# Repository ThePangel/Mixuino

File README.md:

<h1 align="center">Mixuino</h1>

<h3 align="center">An Arduino Mixer for windows built with Python</h3>

-----------

- Table of contents
	- Description
	- Built with
	- Usage
		- UI
		- Config file
	- Getting started
		- Software
			- Required libraries
			- Python
		- Hardware
			- Required hardware
			- Circuit diagram
	- Roadmap!
	- Contributing?
	- Contact
	- Acknowledgement/Credit

---------

Mixuino is a windows audio mixer build with on a Arduino nano and controlled by a python program. It uses 4 slide potentiometers feeding analog input into an Arduino nano that sends the values through serial to a python scripts that handles volume management in the windows machine. You can also add an optional push button to mute/un-mute the speakers. 

I also have made a PCB for ease of instalation + a 3D printable enclosure for the latter so you can build your own Mixer.

This is my first Arduino projects and first *"big"* program so please bear with me :)

-----
## Built with:

- 
- 
- 

---
## Usage 

### UI

Each checkbox corresponds to a running process and/or a process stored in the config file, ones stored (therefore selected) are checked, moving that slider will change the volume of selected processes (1<sup>st</sup> slider is for master volume)

Hide to systray hides the window, the window can be revealed again from the systray icon option  ``Show`` 

There is also a checkbox than when checked changes the ``hideDefault`` value if you want the window to be hidden at startup

The options available refreshes and changes (if new programs are opened or others closed) when the mouse hovers any of the scrollable frames

To close the application you can just close this window or close it with the ``Exit`` option in the systray icon

### Config file

To run the program you require [processes.yaml](processes.yaml) file with the structure : 
```yaml
hideDefault: false
slider1: []	
slider2: []
slider3: []

```
The values are the processes each slide changes and can be changed manually or through the UI

---
## Getting started

### Software

#### Required libraries:

##### Python
- Using pip

```python
comtypes==1.2.0 # To communicate with the ports

Pillow==10.1.0 # For opening the image for the systray icon

pycaw==20230407 # For audio handling

pyserial==3.5 # To read the serial data sent from the arduino

pystray==0.19.5 # To create and manage the systray icon

PyYAML==6.0.1 # To edit the Yaml config file

customtkinter==5.2.1 # To build the UI
```

```console
pip install comtypes

pip install Pillow

pip install pycaw

pip install pyserial

pip install pystray

pip install PyYAML

pip install customtkinter
```
##### Nothing needed for the Arduino

### Hardware 
#### Required hardware

- Arduino nano (you could use any Arduino tho)
- 4 (or more if you want to expand) slide potentiometers
- Optional push button for muting

##### Circuit diagram

---

## Roadmap!

- [x] Slider 3D Models for 3D printing! (7/7/2024)
- [x] GUI to select which slides control which process (30/12/2023)
- [x] Mixuino PCB (7/7/2024)

---
## Contributing?

- Feel free to open up any issues or ask for features in the issues tab!
- If you want to contribute directly make sure to fork the repo and submit a pull request for me to review.

---
## Contact

Feel free to contact me [@ThePangel_](https://twitter.com/thepangel_) on Twitter/X or DM me on discord @thepangel

----
## Acknowledgement/Credit

- Logo: Inés D'Olha

---

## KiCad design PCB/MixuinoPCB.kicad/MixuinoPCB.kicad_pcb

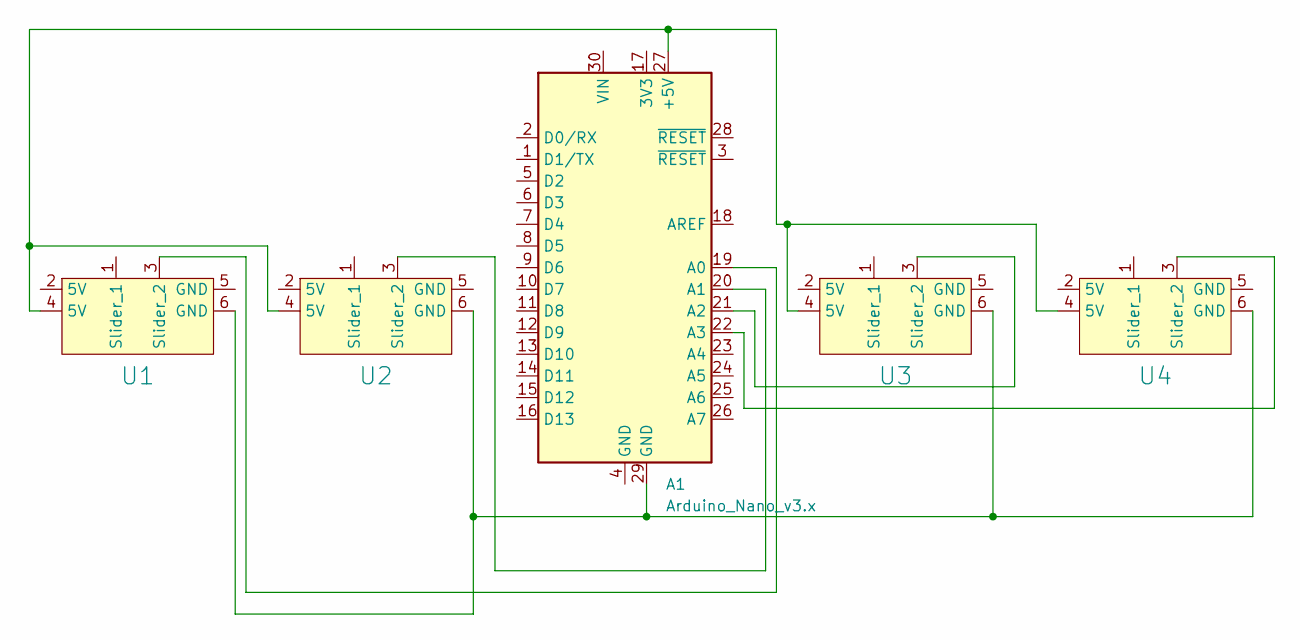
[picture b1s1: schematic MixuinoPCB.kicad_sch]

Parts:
A1: Arduino_Nano_v3.x; Arduino_Nano
U1, U2, U3, U4: Slide Potentiometer - B103

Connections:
unnamed: A1.27 (+5V), U1.4 (5V), U2.4 (5V), U3.4 (5V), U4.4 (5V)
unnamed: A1.19 (A0), U1.3 (Slider_2)
unnamed: A1.20 (A1), U2.3 (Slider_2)
unnamed: A1.21 (A2), U3.3 (Slider_2)
unnamed: A1.22 (A3), U4.3 (Slider_2)
unnamed: A1.29 (GND), U1.6 (GND), U2.6 (GND), U3.6 (GND), U4.6 (GND)

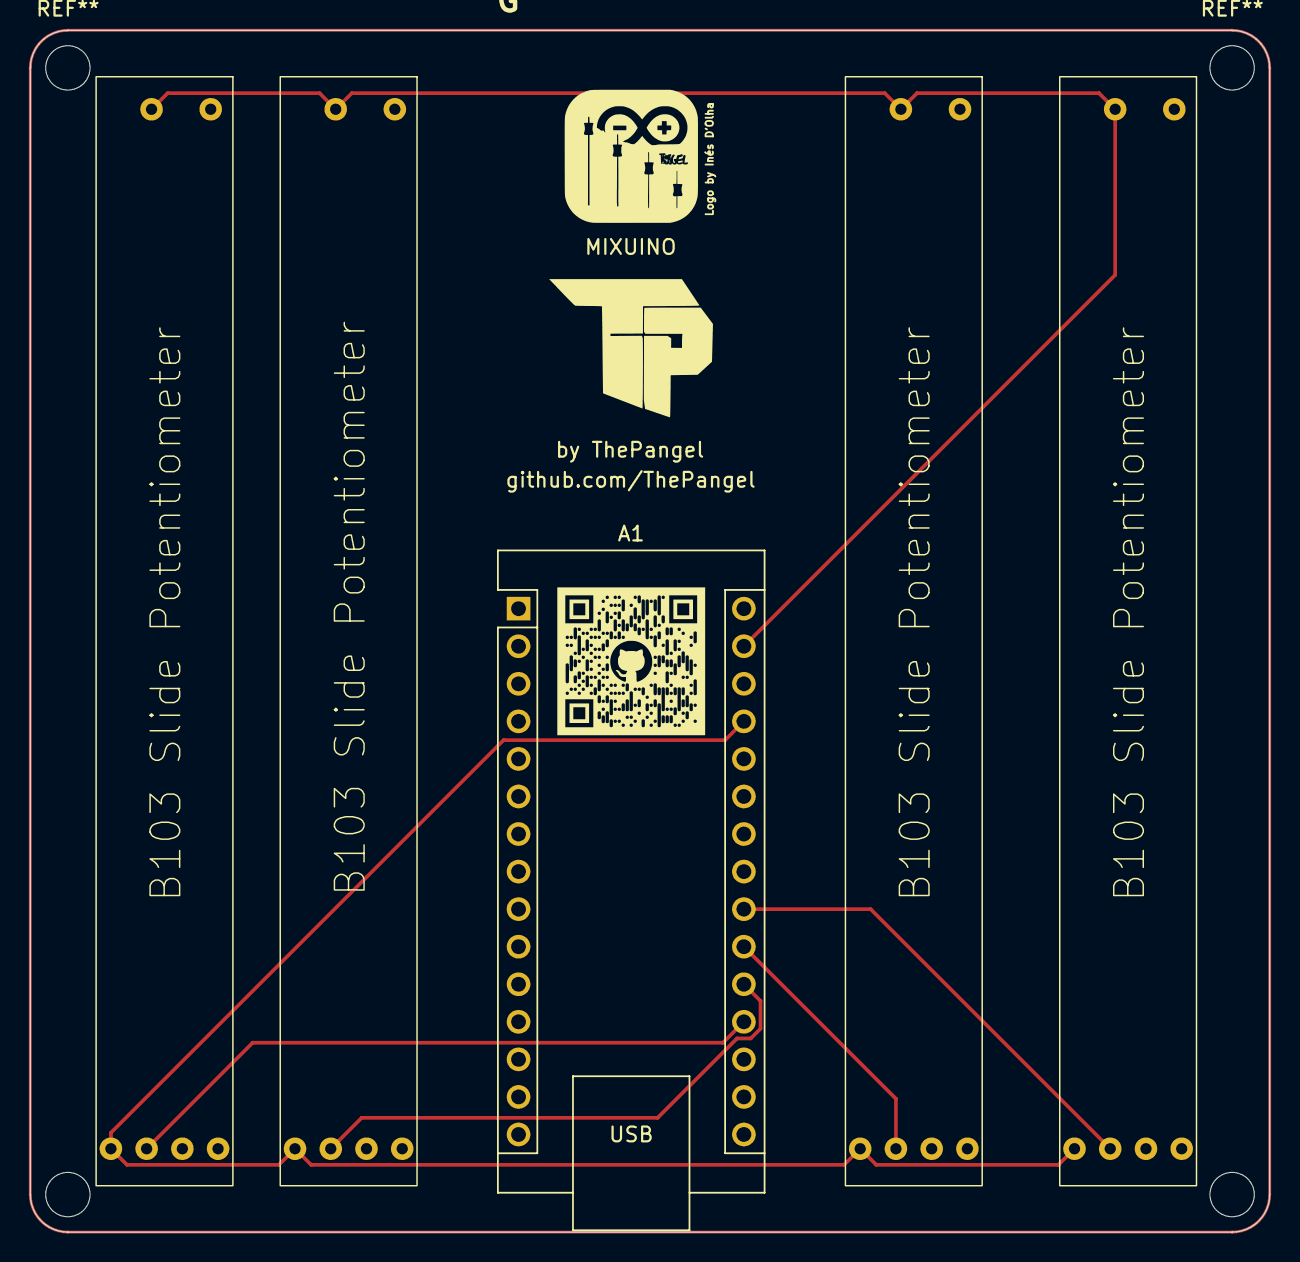
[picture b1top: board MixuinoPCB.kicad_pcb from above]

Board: 2 copper layers, 83.8 x 81.3 mm, 6 parts (0 on the bottom side), 6 nets.

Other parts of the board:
REF: LOGO

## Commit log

2023-12-04 Create LICENSE.md
    added license
2023-12-04 Test
2023-12-06 1st README
2023-12-07 Adding diagram image
2023-12-07 Trying using pdf for the diagram
2023-12-07 Testing readme pdf
2023-12-20 First main version!
2023-12-21 Minor optimization and roadmap change
2023-12-30 UI update!
2023-12-30 GitIgnore update/test
2024-03-25 Fixed disconnect breaking the program (now able to reconnect)
2024-03-25 Now window can be hidden on startup trough a checkbox, value is saved to processes.yaml file, changed readme to accomodate this change
2024-03-31 Simplified both scripts (python, Arduino), optimization and clean-up. huge update!
2024-04-01 Multiple programs per slider, new UI format, new config file. Huge Update!
2024-04-01 Quick README fix
2024-05-03 Fixed UI not showing the hide to systray button and toggle by changing the UI layout, which I think is now better.
2024-07-07 Added PCB and 3D enclosure STL and STEP files
2024-07-07 Little README fix
2024-07-07 Update README.md (again 😭)
2024-07-07 I am dumb
